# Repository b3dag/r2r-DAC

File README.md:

# r2r-DAC
DIY r2r dac using i2s wich get converted by another board.

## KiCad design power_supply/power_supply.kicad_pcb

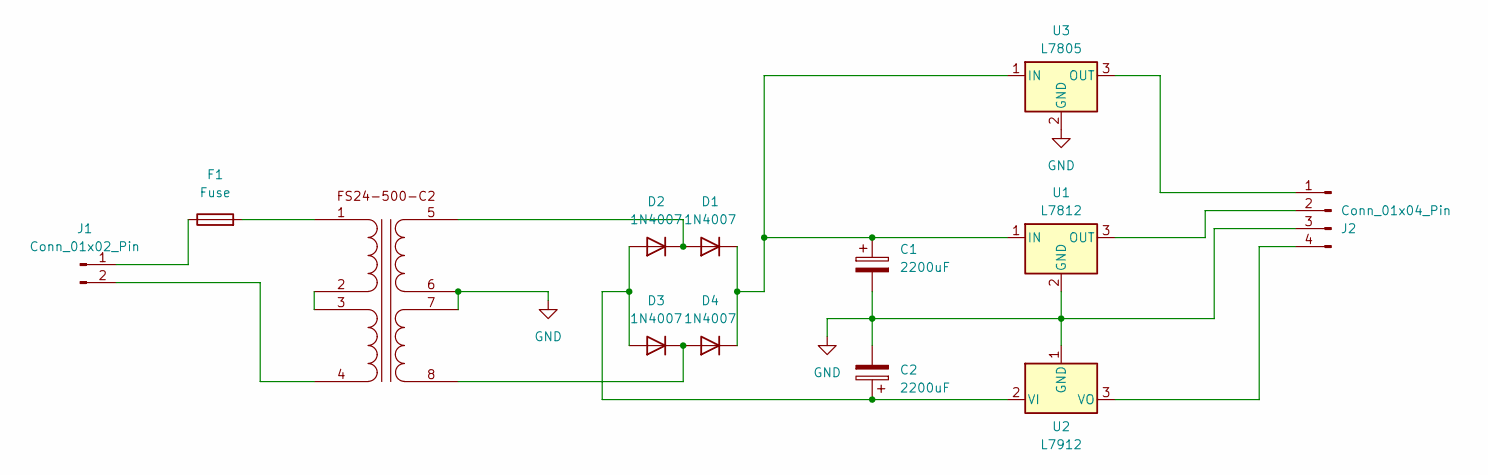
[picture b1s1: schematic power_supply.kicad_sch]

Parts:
C1, C2: 2200uF; CP_Radial_D12.5mm_P5.00mm
D1, D2, D3, D4: 1N4007; D_DO-41_SOD81_P10.16mm_Horizontal
F1: Fuse; Fuseholder_Clip-5x20mm_Littelfuse_111_Inline_P20.00x5.00mm_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
J1: Conn_01x02_Pin; SolderWire-0.5sqmm_1x02_P4.6mm_D0.9mm_OD2.1mm
J2: Conn_01x04_Pin; SolderWire-0.5sqmm_1x04_P4.6mm_D0.9mm_OD2.1mm
T1: FS24-500-C2
U1: L7812; TO-220-3_Vertical
U2: L7912; TO-220-3_Vertical
U3: L7805; TO-220-3_Vertical

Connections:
GND: C1.2, C2.2, J2.3, T1.6, T1.7, U1.2 (GND), U2.1 (GND), U3.2 (GND)
unnamed: D1.2 (A), D2.1 (K), T1.5
unnamed: C1.1, D1.1 (K), D4.1 (K), U1.1 (IN), U3.1 (IN)
unnamed: C2.1, D2.2 (A), D3.2 (A), U2.2 (VI)
unnamed: D3.1 (K), D4.2 (A), T1.8
unnamed: F1.2, T1.1
unnamed 6: F1.1, J1.1; also elsewhere on the board
unnamed 7: J1.2, T1.4; also elsewhere on the board
unnamed: J2.1, U3.3 (OUT)
unnamed: J2.2, U1.3 (OUT)
unnamed: J2.4, U2.3 (VO)
unnamed: T1.2, T1.3

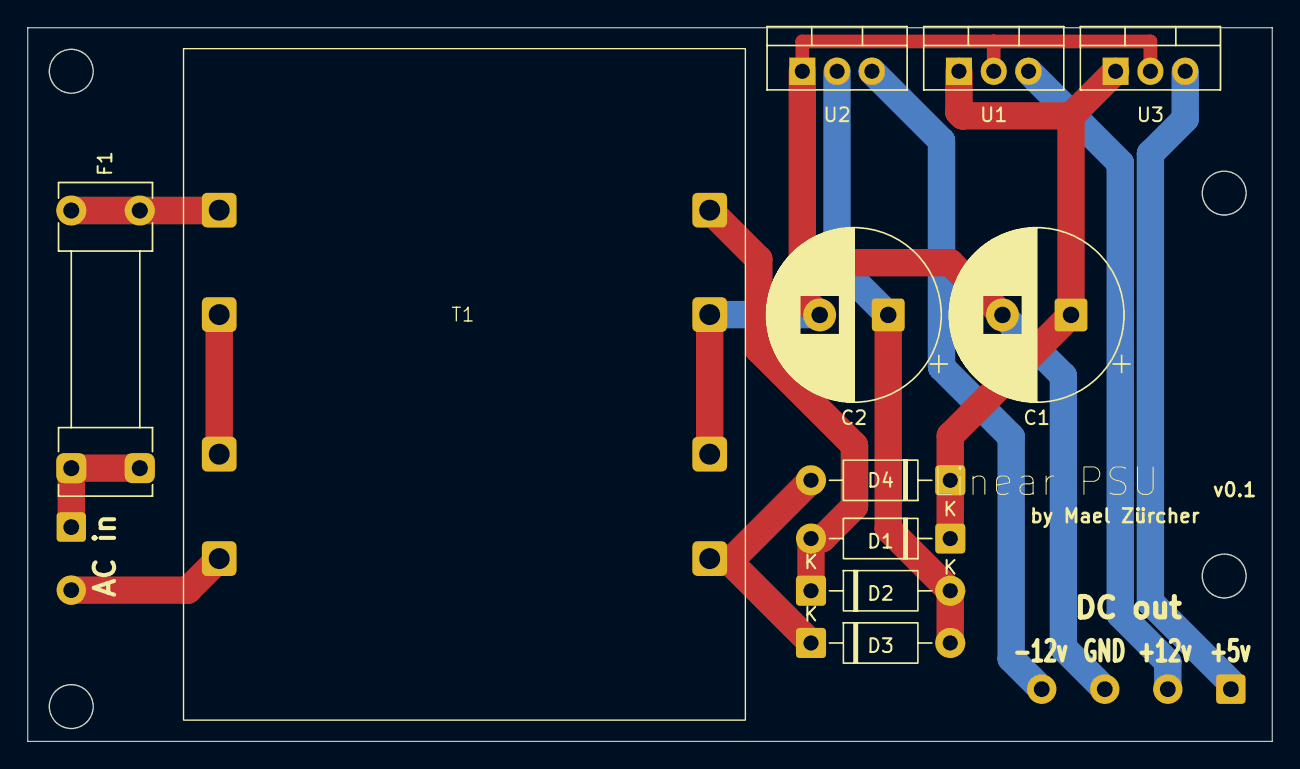
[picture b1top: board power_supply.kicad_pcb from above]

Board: 2 copper layers, 90.8 x 52.1 mm, 13 parts (0 on the bottom side), 12 nets.

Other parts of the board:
AC in: Conn_01x02_Pin; SolderWire-0.5sqmm_1x02_P4.6mm_D0.9mm_OD2.1mm

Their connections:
unnamed 6: AC in.1; also elsewhere on the board
unnamed 7: AC in.2; also elsewhere on the board

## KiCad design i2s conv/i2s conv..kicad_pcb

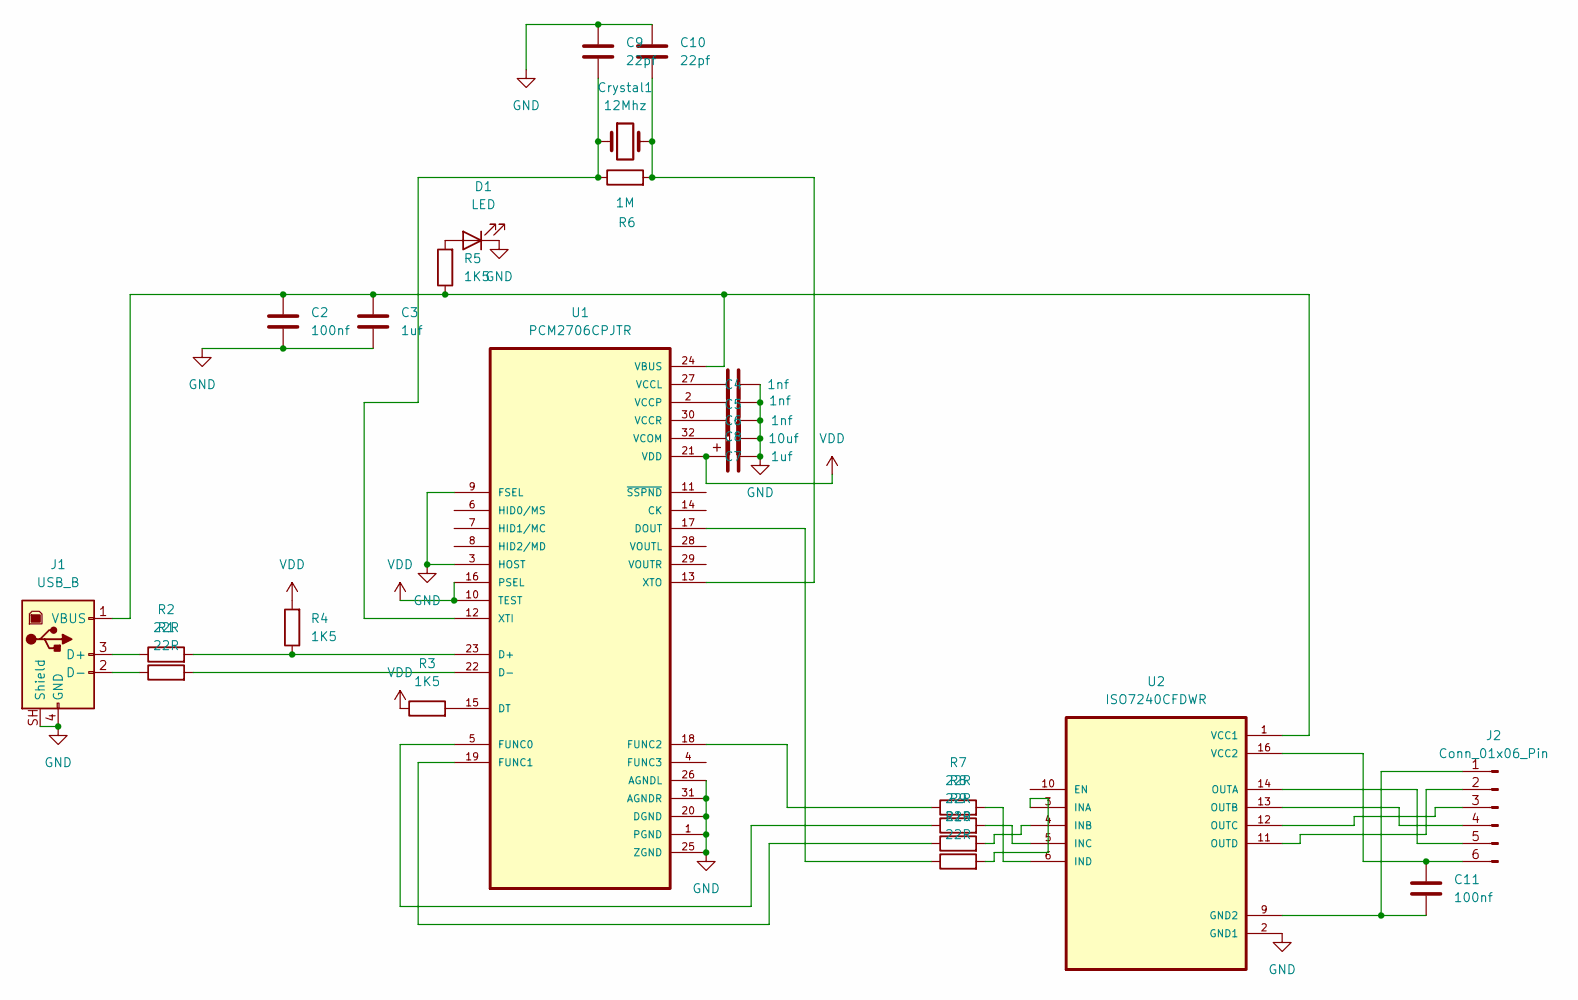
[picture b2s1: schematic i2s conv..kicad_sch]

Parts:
C2, C11: 100nf; C_0805_2012Metric_Pad1.18x1.45mm_HandSolder
C3, C7: 1uf; C_0805_2012Metric_Pad1.18x1.45mm_HandSolder
C4, C5, C6: 1nf; C_0805_2012Metric_Pad1.18x1.45mm_HandSolder
C8: 10uf; C_Radial_D6.3mm_H7.0mm_P2.50mm
C9, C10: 22pf; C_0805_2012Metric_Pad1.18x1.45mm_HandSolder
Crystal1: 12Mhz; Crystal_HC49-4H_Vertical
D1: LED; LED_D5.0mm
J1: USB_B; USB_B_OST_USB-B1HSxx_Horizontal
J2: Conn_01x06_Pin; PinHeader_1x06_P2.54mm_Vertical
R1, R2, R7, R8, R9, R10: 22R; R_0805_2012Metric_Pad1.20x1.40mm_HandSolder
R3, R4, R5: 1K5; R_0805_2012Metric_Pad1.20x1.40mm_HandSolder
R6: 1M; R_0805_2012Metric_Pad1.20x1.40mm_HandSolder
U1: PCM2706CPJTR; QFP80P900X900X120-32N
U2: ISO7240CFDWR; SOIC127P1030X265-16N

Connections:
GND: C2.2, C3.2, C4.2, C5.2, C6.2, C7.2, C8.2, C9.1, C10.1, D1.1 (K), J1.4 (GND), J1.SH (Shield), U1.1 (PGND), U1.3 (HOST), U1.9 (FSEL), U1.20 (DGND), U1.25 (ZGND), U1.26 (AGNDL), U1.31 (AGNDR), U2.2 (GND1), U2.8 (GND1)
GND2: C11.2, J2.1, U2.9 (GND2), U2.15 (GND2)
unnamed: D1.2 (A), R5.2
unnamed: J1.3 (D+), R2.1
unnamed: J1.2 (D-), R1.1
unnamed: C2.1, C3.1, J1.1 (VBUS), R5.1, U1.24 (VBUS), U2.1 (VCC1)
unnamed: J2.2, U2.11 (OUTD)
unnamed: J2.3, U2.12 (OUTC)
unnamed: J2.4, U2.13 (OUTB)
unnamed: J2.5, U2.14 (OUTA)
unnamed: C11.1, J2.6, U2.16 (VCC2)
unnamed: R2.2, R4.1, U1.23 (D+)
unnamed: R1.2, U1.22 (D-)
unnamed: R10.1, U1.17 (DOUT)
unnamed: R3.2, U1.15 (DT)
unnamed: R8.1, U1.5 (FUNC0)
unnamed: R9.1, U1.19 (FUNC1)
unnamed: R7.1, U1.18 (FUNC2)
unnamed: C4.1, U1.27 (VCCL)
unnamed: C5.1, U1.2 (VCCP)
unnamed: C6.1, U1.30 (VCCR)
unnamed: C8.1, U1.32 (VCOM)
unnamed: C9.2, Crystal1.1, R6.1, U1.12 (XTI)
unnamed: C10.2, Crystal1.2, R6.2, U1.13 (XTO)
unnamed: R10.2, U2.3 (INA)
unnamed: R9.2, U2.4 (INB)
unnamed: R8.2, U2.5 (INC)
unnamed: R7.2, U2.6 (IND)
VDD: C7.1, R3.1, R4.2, U1.10 (TEST), U1.16 (PSEL), U1.21 (VDD)

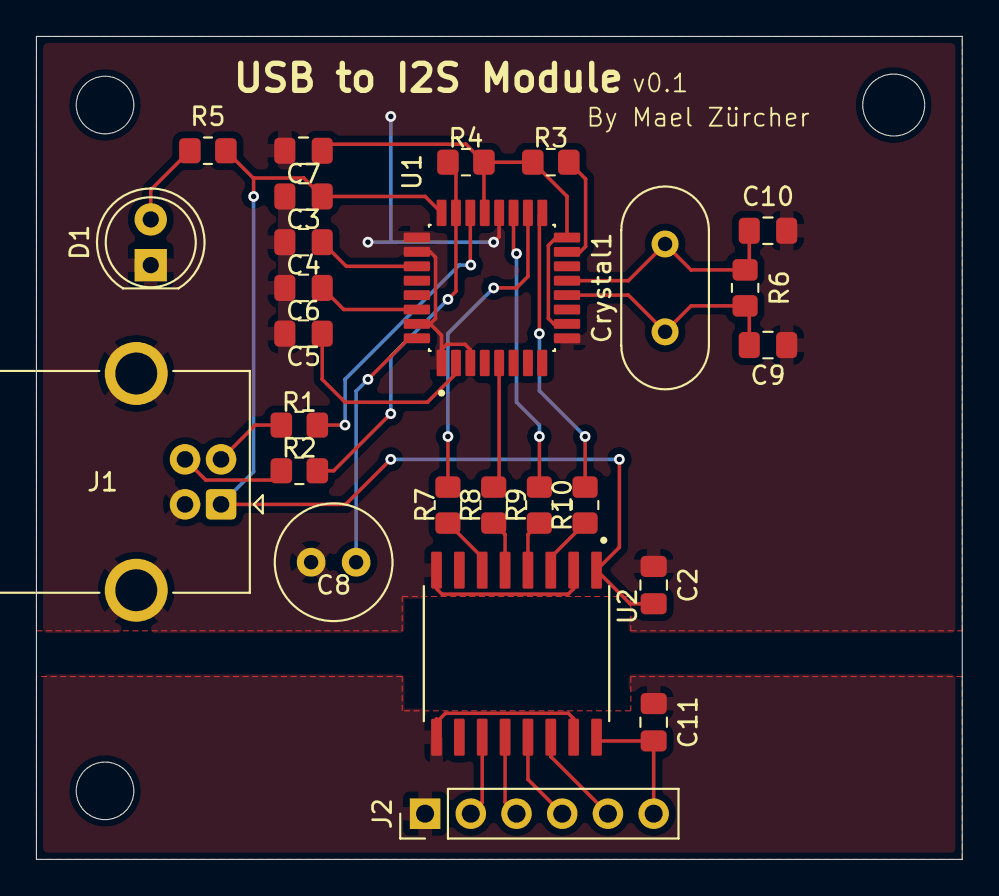
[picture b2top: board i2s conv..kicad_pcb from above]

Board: 2 copper layers, 51.4 x 45.7 mm, 26 parts (0 on the bottom side), 29 nets.

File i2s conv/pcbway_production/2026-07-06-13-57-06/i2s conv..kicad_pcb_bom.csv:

Designator,Quantity,Value,Footprint,Package,MPN,DNP,Mount_Type,Description,KiLib_Generator,Sim.Pins,MF,Price,SnapEDA_Link,MP,Availability,Check_prices
"C10, C9",2,22pf,C_0805_2012Metric_Pad1.18x1.45mm_HandSolder,,,,smt,Unpolarized capacitor,SMD_2terminal_chip_molded,,,,,,,
"C11, C2",2,100nf,C_0805_2012Metric_Pad1.18x1.45mm_HandSolder,,,,smt,Unpolarized capacitor,SMD_2terminal_chip_molded,,,,,,,
"C3, C7",2,1uf,C_0805_2012Metric_Pad1.18x1.45mm_HandSolder,,,,smt,Unpolarized capacitor,SMD_2terminal_chip_molded,,,,,,,
"C4, C5, C6",3,1nf,C_0805_2012Metric_Pad1.18x1.45mm_HandSolder,,,,smt,Unpolarized capacitor,SMD_2terminal_chip_molded,,,,,,,
C8,1,10uf,C_Radial_D6.3mm_H7.0mm_P2.50mm,,,,tht,Polarized capacitor,capacitor/THT/other,,,,,,,
Crystal1,1,12Mhz,Crystal_HC49-4H_Vertical,,,,tht,Two pin crystal,crystal_resonator_oscillator,,,,,,,
D1,1,LED,LED_D5.0mm,,,,tht,Light emitting diode,LED/THT,1=K 2=A,,,,,,
J1,1,USB_B,USB_B_OST_USB-B1HSxx_Horizontal,,,,tht,USB Type B connector,,,,,,,,
J2,1,Conn_01x06_Pin,PinHeader_1x06_P2.54mm_Vertical,,,,tht,"Generic connector, single row, 01x06, script generated",connector/pin_header_socket,,,,,,,
"R1, R10, R2, R7, R8, R9",6,22R,R_0805_2012Metric_Pad1.20x1.40mm_HandSolder,,,,smt,Resistor,SMD_2terminal_chip_molded,,,,,,,
"R3, R4, R5",3,1K5,R_0805_2012Metric_Pad1.20x1.40mm_HandSolder,,,,smt,Resistor,SMD_2terminal_chip_molded,,,,,,,
R6,1,1M,R_0805_2012Metric_Pad1.20x1.40mm_HandSolder,,,,smt,Resistor,SMD_2terminal_chip_molded,,,,,,,
U1,1,PCM2706CPJTR,QFP80P900X900X120-32N,TQFP-32 Texas Instruments,,,smt,"98dB SNR Stereo Full Speed DAC with line-out and S/PDIF output, Bus/Self-powered (I2S)",,,Texas Instruments,None,https://www.snapeda.com/parts/PCM2706CPJTR/Texas+Instruments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,PCM2706CPJTR,In Stock,https://www.snapeda.com/parts/PCM2706CPJTR/Texas+Instruments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
U2,1,ISO7240CFDWR,SOIC127P1030X265-16N,SOIC-16 Texas Instruments,,,smt,"Quad-channel, 4/0, 25-Mbps, default output low digital isolator",,,Texas Instruments,None,https://www.snapeda.com/parts/ISO7240CFDWR/Texas+Instruments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,ISO7240CFDWR,In Stock,https://www.snapeda.com/parts/ISO7240CFDWR/Texas+Instruments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

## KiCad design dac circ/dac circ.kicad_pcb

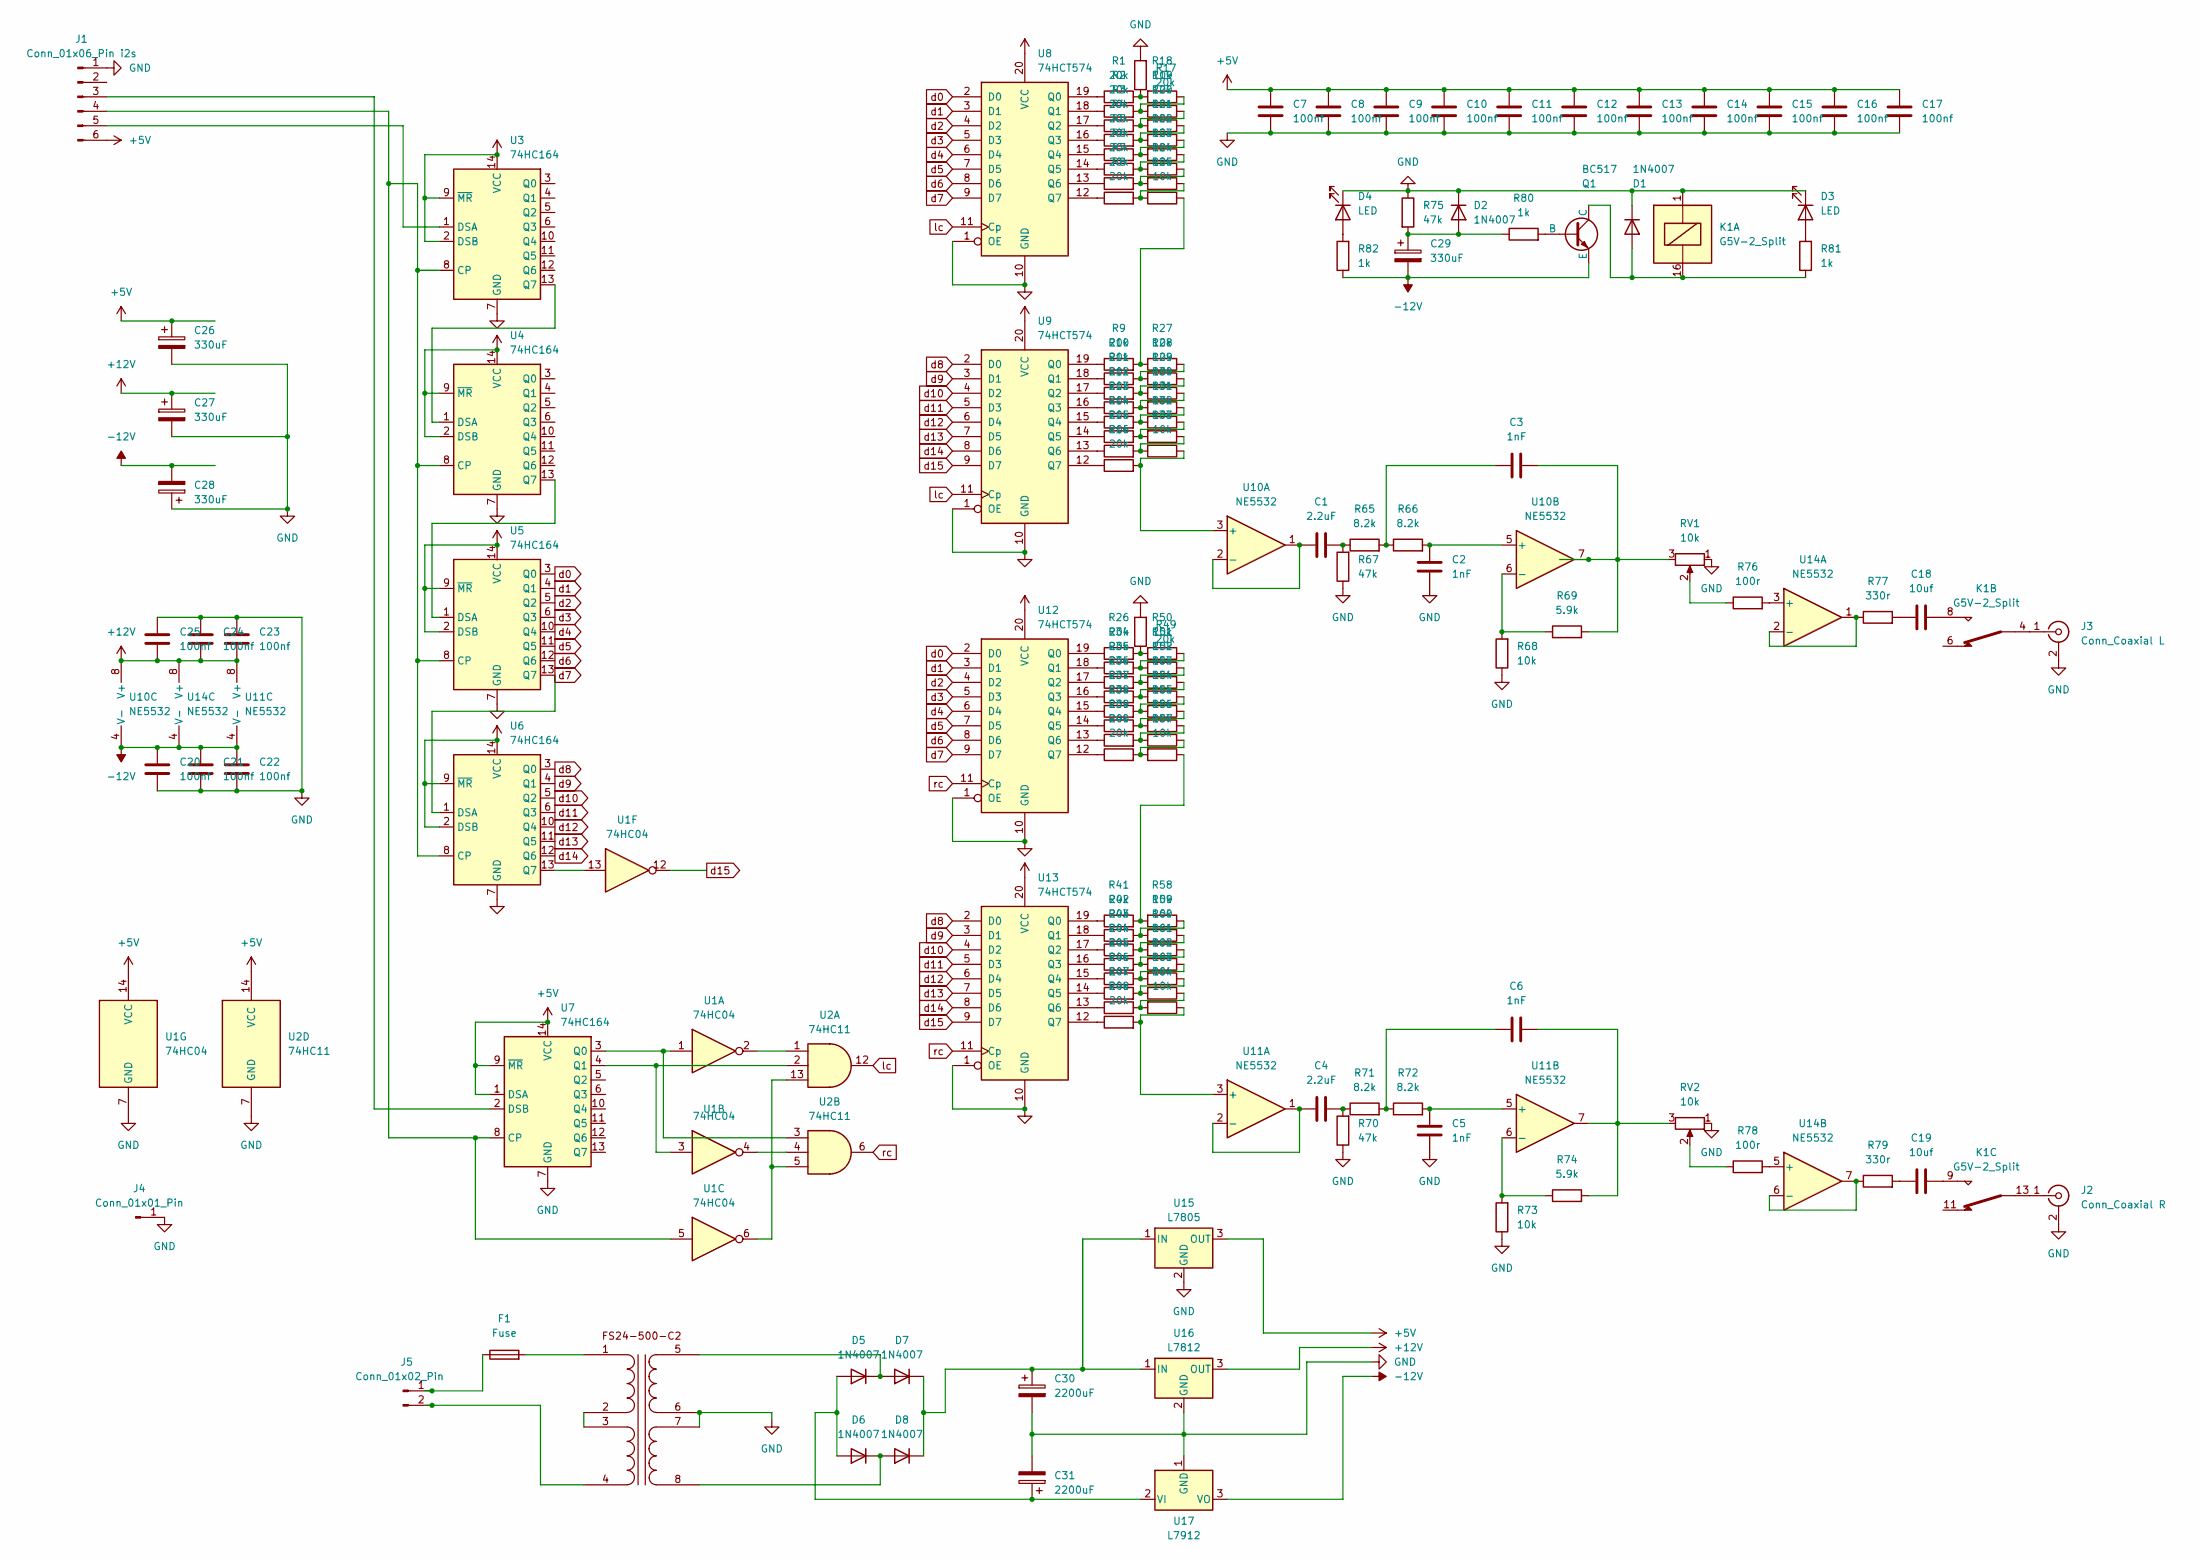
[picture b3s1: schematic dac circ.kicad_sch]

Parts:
C1, C4: 2.2uF; C_Radial_D5.0mm_H11.0mm_P2.00mm
C2, C3, C5, C6: 1nF; C_Disc_D5.0mm_W2.5mm_P5.00mm
C7, C8, C9, C10, C11, C12, C13, C14, C15, C16, C17, C20, C21, C22, C23, C24, C25: 100nf; C_Disc_D5.0mm_W2.5mm_P5.00mm
C18, C19: 10uf; C_Radial_D5.0mm_H11.0mm_P2.00mm
C26, C27, C28, C29: 330uF; CP_Radial_D12.5mm_P5.00mm
C30, C31: 2200uF; CP_Radial_D12.5mm_P5.00mm
D1, D2: 1N4007; D_A-405_P7.62mm_Horizontal
D3, D4: LED; LED_D5.0mm
D5, D6, D7, D8: 1N4007; D_DO-41_SOD81_P10.16mm_Horizontal
F1: Fuse; Fuseholder_Clip-5x20mm_Littelfuse_111_Lateral_P18.80x5.00mm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
J1: Conn_01x06_Pin i2s; PinHeader_1x06_P2.54mm_Vertical
J2: Conn_Coaxial R; SolderWire-0.5sqmm_1x02_P4.6mm_D0.9mm_OD2.1mm
J3: Conn_Coaxial L; SolderWire-0.25sqmm_1x02_P4.5mm_D0.65mm_OD2mm
J4: Conn_01x01_Pin; SolderWire-0.5sqmm_1x01_D0.9mm_OD2.1mm
J5: Conn_01x02_Pin; SolderWire-0.5sqmm_1x02_P4.6mm_D0.9mm_OD2.1mm
K1: G5V-2_Split; Relay_DPDT_Omron_G5V-2
Q1: BC517; TO-92L_HandSolder
R1, R2, R3, R4, R5, R6, R7, R8, R9, R10, R11, R12, R13, R14, R15, R16, R17, R26, R34, R35, R36, R37, R38, R39, R40, R41, R42, R43, R44, R45, R46, R47, R48, R49: 20k; R_Axial_DIN0207_L6.3mm_D2.5mm_P7.62mm_Horizontal
R18, R19, R20, R21, R22, R23, R24, R25, R27, R28, R29, R30, R31, R32, R33, R50, R51, R52, R53, R54, R55, R56, R57, R58, R59, R60, R61, R62, R63, R64, R68, R73: 10k; R_Axial_DIN0207_L6.3mm_D2.5mm_P7.62mm_Horizontal
R65, R66, R71, R72: 8.2k; R_Axial_DIN0207_L6.3mm_D2.5mm_P7.62mm_Horizontal
R67, R70, R75: 47k; R_Axial_DIN0207_L6.3mm_D2.5mm_P7.62mm_Horizontal
R69, R74: 5.9k; R_Axial_DIN0207_L6.3mm_D2.5mm_P7.62mm_Horizontal
R76, R78: 100r; R_Axial_DIN0207_L6.3mm_D2.5mm_P7.62mm_Horizontal
R77, R79: 330r; R_Axial_DIN0207_L6.3mm_D2.5mm_P7.62mm_Horizontal
R80, R81, R82: 1k; R_Axial_DIN0207_L6.3mm_D2.5mm_P7.62mm_Horizontal
RV1, RV2: 10k; Potentiometer_Bourns_3296W_Vertical
T1: TRANSFORMER_FS24-500-C2
U1: 74HC04; DIP-14_W7.62mm
U2: 74HC11; DIP-14_W7.62mm
U3, U4, U5, U6, U7: 74HC164; DIP-14_W7.62mm
U8, U9, U12, U13: 74HCT574; DIP-20_W7.62mm
U10, U11, U14: NE5532; DIP-8_W7.62mm
U15: L7805; TO-220-3_Horizontal_TabUp
U16: L7812; TO-220-3_Horizontal_TabUp
U17: L7912; TO-220-3_Horizontal_TabUp

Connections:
+5V: C7.1, C8.1, C9.1, C10.1, C11.1, C12.1, C13.1, C14.1, C15.1, C16.1, C17.1, C26.1, J1.6, U1.14 (VCC), U2.14 (VCC), U3.2 (DSB), U3.9 (~MR), U3.14 (VCC), U4.2 (DSB), U4.9 (~MR), U4.14 (VCC), U5.2 (DSB), U5.9 (~MR), U5.14 (VCC), U6.2 (DSB), U6.9 (~MR), U6.14 (VCC), U7.1 (DSA), U7.9 (~MR), U7.14 (VCC), U8.20 (VCC), U9.20 (VCC), U12.20 (VCC), U13.20 (VCC), U15.3 (OUT)
+12V: C23.2, C24.2, C25.2, C27.1, U10.8 (V+), U11.8 (V+), U14.8 (V+), U16.3 (OUT)
-12V: C20.1, C21.1, C22.1, C28.2, C29.2, Q1.3 (E), R82.1, U10.4 (V-), U11.4 (V-), U14.4 (V-), U17.3 (VO)
GND: C2.2, C5.2, C7.2, C8.2, C9.2, C10.2, C11.2, C12.2, C13.2, C14.2, C15.2, C16.2, C17.2, C20.2, C21.2, C22.2, C23.1, C24.1, C25.1, C26.2, C27.2, C28.1, C30.2, C31.2, D1.1 (K), D2.1 (K), D3.1 (K), D4.1 (K), J1.1, J2.2 (Ext), J3.2 (Ext), J4.1 (Pin_1_1), K1.1, R17.2, R49.2, R67.1, R68.1, R70.1, R73.1, R75.1, RV1.1, RV2.1, T1.6, T1.7, U1.7 (GND), U2.7 (GND), U3.7 (GND), U4.7 (GND), U5.7 (GND), U6.7 (GND), U7.7 (GND), U8.1 (OE), U8.10 (GND), U9.1 (OE), U9.10 (GND), U12.1 (OE), U12.10 (GND), U13.1 (OE), U13.10 (GND), U15.2 (GND), U16.2 (GND), U17.1 (GND)
unnamed: C1.2, R65.1, R67.2
unnamed: C3.1, R65.2, R66.1
unnamed: C3.2, R69.2, RV1.3, U10.7
unnamed: C4.2, R70.2, R71.1
unnamed: C6.1, R71.2, R72.1
unnamed: C6.2, R74.2, RV2.3, U11.7
unnamed: C18.1, R77.2
unnamed: C18.2, K1.8
unnamed: C19.1, R79.2
unnamed: C19.2, K1.9
unnamed: D1.2 (A), K1.16, Q1.1 (C), R81.1
unnamed: C29.1, D2.2 (A), R75.2, R80.1
unnamed: D3.2 (A), R81.2
unnamed: D4.2 (A), R82.2
unnamed: C31.1, D5.2 (A), D6.2 (A), U17.2 (VI)
unnamed: D5.1 (K), D7.2 (A), T1.5
unnamed: D6.1 (K), D8.2 (A), T1.8
unnamed: C30.1, D7.1 (K), D8.1 (K), U15.1 (IN), U16.1 (IN)
unnamed: F1.2, T1.1
unnamed: J1.3, U7.2 (DSB)
unnamed: J1.4, U1.5, U3.8 (CP), U4.8 (CP), U5.8 (CP), U6.8 (CP), U7.8 (CP)
unnamed: J1.5, U3.1 (DSA)
unnamed: J2.1 (In), K1.13
unnamed: J3.1 (In), K1.4
unnamed: F1.1, J5.1
unnamed: J5.2, T1.4
unnamed: Q1.2 (B), R80.2
unnamed: R1.2, R17.1, R18.2
unnamed: R10.2, R27.1, R28.2
unnamed: R11.2, R28.1, R29.2
unnamed: R12.2, R29.1, R30.2
unnamed: R13.2, R30.1, R31.2
unnamed: R14.2, R31.1, R32.2
unnamed: R15.2, R32.1, R33.2
unnamed: R2.2, R18.1, R19.2
unnamed: R3.2, R19.1, R20.2
unnamed: R4.2, R20.1, R21.2
unnamed: R5.2, R21.1, R22.2
unnamed: R6.2, R22.1, R23.2
unnamed: R7.2, R23.1, R24.2
unnamed: R8.2, R24.1, R25.2
unnamed: R9.2, R25.1, R27.2
unnamed: R26.2, R49.1, R50.2
unnamed: R34.2, R50.1, R51.2
unnamed: R35.2, R51.1, R52.2
unnamed: R36.2, R52.1, R53.2
unnamed: R37.2, R53.1, R54.2
unnamed: R38.2, R54.1, R55.2
unnamed: R39.2, R55.1, R56.2
unnamed: R40.2, R56.1, R57.2
unnamed: R41.2, R57.1, R58.2
unnamed: R42.2, R58.1, R59.2
unnamed: R43.2, R59.1, R60.2
unnamed: R44.2, R60.1, R61.2
unnamed: R45.2, R61.1, R62.2
unnamed: R46.2, R62.1, R63.2
unnamed: R47.2, R63.1, R64.2
unnamed: R76.1, RV1.2
unnamed: R78.1, RV2.2
unnamed: T1.2, T1.3
unnamed: U1.2, U2.1
unnamed: U1.4, U2.4
unnamed: U1.6, U2.5, U2.13
unnamed: U3.13 (Q7), U4.1 (DSA)
unnamed: U4.13 (Q7), U5.1 (DSA)
unnamed: U1.13, U6.13 (Q7)
unnamed: U1.1, U2.3, U7.3 (Q0)
unnamed: U1.3, U2.2, U7.4 (Q1)
unnamed: R1.1, U8.19 (Q0)
unnamed: R2.1, U8.18 (Q1)
unnamed: R3.1, U8.17 (Q2)
unnamed: R4.1, U8.16 (Q3)
unnamed: R5.1, U8.15 (Q4)
unnamed: R6.1, U8.14 (Q5)
unnamed: R7.1, U8.13 (Q6)
unnamed: R8.1, U8.12 (Q7)
unnamed: R9.1, U9.19 (Q0)
unnamed: R10.1, U9.18 (Q1)
unnamed: R11.1, U9.17 (Q2)
unnamed: R12.1, U9.16 (Q3)
unnamed: R13.1, U9.15 (Q4)
unnamed: R14.1, U9.14 (Q5)
unnamed: R15.1, U9.13 (Q6)
unnamed: R16.1, U9.12 (Q7)
unnamed: R16.2, R33.1, U10.3 (+)
unnamed: C1.1, U10.1, U10.2 (-)
unnamed: C2.1, R66.2, U10.5 (+)
unnamed: R68.2, R69.1, U10.6 (-)
unnamed: R48.2, R64.1, U11.3 (+)
unnamed: C4.1, U11.1, U11.2 (-)
unnamed: C5.1, R72.2, U11.5 (+)
unnamed: R73.2, R74.1, U11.6 (-)
unnamed: R26.1, U12.19 (Q0)
unnamed: R34.1, U12.18 (Q1)
unnamed: R35.1, U12.17 (Q2)
unnamed: R36.1, U12.16 (Q3)
unnamed: R37.1, U12.15 (Q4)
unnamed: R38.1, U12.14 (Q5)
unnamed: R39.1, U12.13 (Q6)
unnamed: R40.1, U12.12 (Q7)
unnamed: R41.1, U13.19 (Q0)
unnamed: R42.1, U13.18 (Q1)
unnamed: R43.1, U13.17 (Q2)
unnamed: R44.1, U13.16 (Q3)
unnamed: R45.1, U13.15 (Q4)
unnamed: R46.1, U13.14 (Q5)
unnamed: R47.1, U13.13 (Q6)
unnamed: R48.1, U13.12 (Q7)
unnamed: R76.2, U14.3 (+)
unnamed: R77.1, U14.1, U14.2 (-)
unnamed: R78.2, U14.5 (+)
unnamed: R79.1, U14.6 (-), U14.7
d0: U5.3 (Q0), U8.2 (D0), U12.2 (D0)
d1: U5.4 (Q1), U8.3 (D1), U12.3 (D1)
d2: U5.5 (Q2), U8.4 (D2), U12.4 (D2)
d3: U5.6 (Q3), U8.5 (D3), U12.5 (D3)
d4: U5.10 (Q4), U8.6 (D4), U12.6 (D4)
d5: U5.11 (Q5), U8.7 (D5), U12.7 (D5)
d6: U5.12 (Q6), U8.8 (D6), U12.8 (D6)
d7: U5.13 (Q7), U6.1 (DSA), U8.9 (D7), U12.9 (D7)
d8: U6.3 (Q0), U9.2 (D0), U13.2 (D0)
d9: U6.4 (Q1), U9.3 (D1), U13.3 (D1)
d10: U6.5 (Q2), U9.4 (D2), U13.4 (D2)
d11: U6.6 (Q3), U9.5 (D3), U13.5 (D3)
d12: U6.10 (Q4), U9.6 (D4), U13.6 (D4)
d13: U6.11 (Q5), U9.7 (D5), U13.7 (D5)
d14: U6.12 (Q6), U9.8 (D6), U13.8 (D6)
d15: U1.12, U9.9 (D7), U13.9 (D7)
lc: U2.12, U8.11 (Cp), U9.11 (Cp)
rc: U2.6, U12.11 (Cp), U13.11 (Cp)

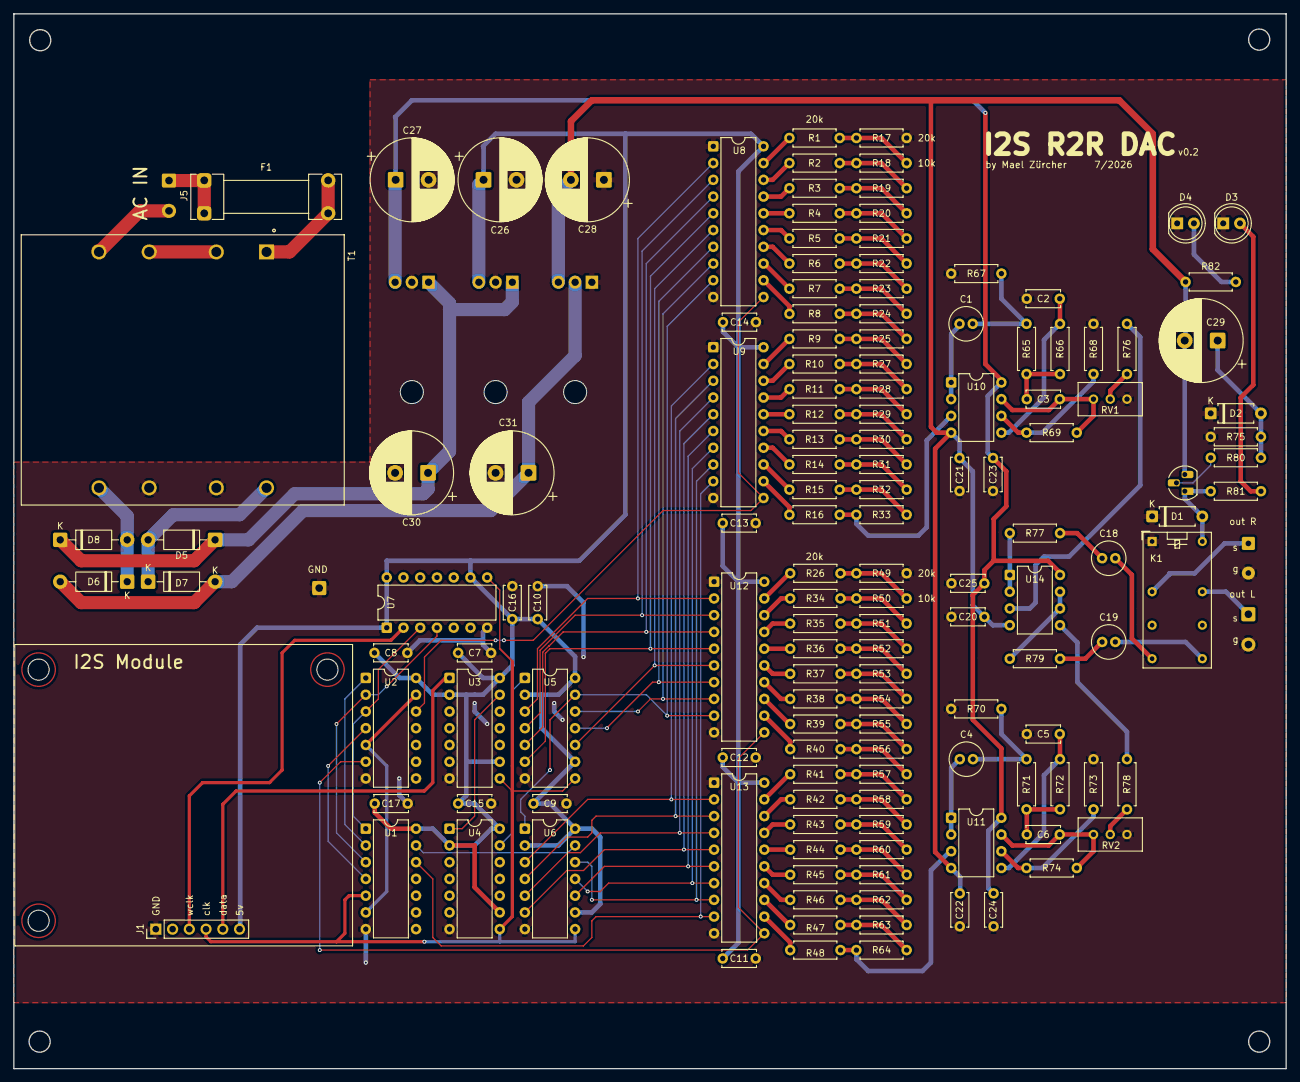
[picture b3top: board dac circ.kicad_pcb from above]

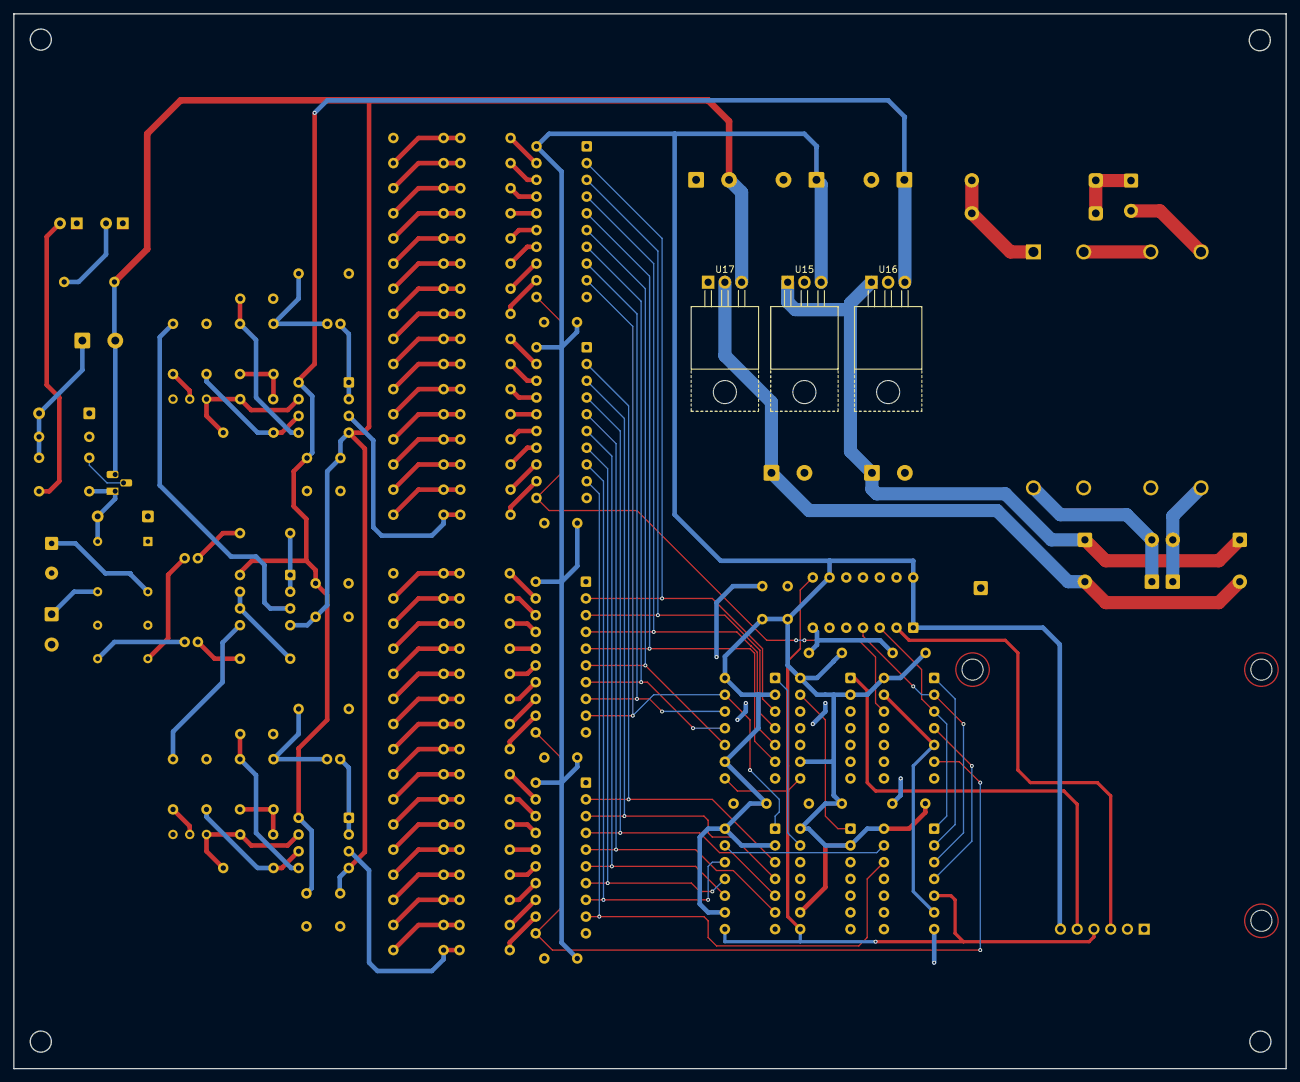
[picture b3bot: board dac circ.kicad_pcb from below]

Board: 2 copper layers, 193.0 x 160.0 mm, 149 parts (3 on the bottom side), 134 nets.

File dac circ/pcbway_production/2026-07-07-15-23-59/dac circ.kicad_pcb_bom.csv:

Designator,Quantity,Value,Footprint,Package,MPN,DNP,Mount_Type,Description,KiLib_Generator,Sim.Device,Sim.Pins,Sim.Type
"C1, C4",2,2.2uF,C_Radial_D5.0mm_H11.0mm_P2.00mm,,,,tht,Unpolarized capacitor,capacitor/THT/other,,,
"C10, C11, C12, C13, C14, C15, C16, C17, C20, C21, C22, C23, C24, C25, C7, C8, C9",17,100nf,C_Disc_D5.0mm_W2.5mm_P5.00mm,,,,tht,Unpolarized capacitor,capacitor/THT/other,,,
"C18, C19",2,10uf,C_Radial_D5.0mm_H11.0mm_P2.00mm,,,,tht,Unpolarized capacitor,capacitor/THT/other,,,
"C2, C3, C5, C6",4,1nF,C_Disc_D5.0mm_W2.5mm_P5.00mm,,,,tht,Unpolarized capacitor,capacitor/THT/other,,,
"C26, C27, C28, C29",4,330uF,CP_Radial_D12.5mm_P5.00mm,,,,tht,Polarized capacitor,capacitor/THT/other,,,
"D1, D2",2,1N4007,D_A-405_P7.62mm_Horizontal,,,,tht,Diode,diode/THT,D,1=K 2=A,
D3,1,LED,LED_D5.0mm,,,,tht,Light emitting diode,LED/THT,,1=K 2=A,
J1,1,Conn_01x06_Pin i2s,PinHeader_1x06_P2.54mm_Vertical,,,,tht,"Generic connector, single row, 01x06, script generated",connector/pin_header_socket,,,
J2,1,Conn_Coaxial R,SolderWire-0.5sqmm_1x02_P4.6mm_D0.9mm_OD2.1mm,,,,tht,"coaxial connector (BNC, SMA, SMB, SMC, Cinch/RCA, LEMO, ...)",connector/wire,,,
J3,1,Conn_Coaxial L,SolderWire-0.25sqmm_1x02_P4.5mm_D0.65mm_OD2mm,,,,tht,"coaxial connector (BNC, SMA, SMB, SMC, Cinch/RCA, LEMO, ...)",connector/wire,,,
J4,1,Conn_01x04_Pin,SolderWire-0.5sqmm_1x04_P4.6mm_D0.9mm_OD2.1mm,,,,tht,"Generic connector, single row, 01x04, script generated",connector/wire,,,
K1,1,G5V-2_Split,Relay_DPDT_Omron_G5V-2,,,,tht,Relay Miniature Omron DPDT,,,,
Q1,1,BC517,TO-92L_HandSolder,,,,tht,"Bipolar transistor symbol for simulation only, substrate tied to the emitter",,NPN,1=C 2=B 3=E,GUMMELPOON
"R1, R10, R11, R12, R13, R14, R15, R16, R17, R2, R26, R3, R34, R35, R36, R37, R38, R39, R4, R40, R41, R42, R43, R44, R45, R46, R47, R48, R49, R5, R6, R7, R8, R9",34,20k,R_Axial_DIN0207_L6.3mm_D2.5mm_P7.62mm_Horizontal,,,,tht,Resistor,resistor/THT,,,
"R18, R19, R20, R21, R22, R23, R24, R25, R27, R28, R29, R30, R31, R32, R33, R50, R51, R52, R53, R54, R55, R56, R57, R58, R59, R60, R61, R62, R63, R64, R68, R73",32,10k,R_Axial_DIN0207_L6.3mm_D2.5mm_P7.62mm_Horizontal,,,,tht,Resistor,resistor/THT,,,
"R65, R66, R71, R72",4,8.2k,R_Axial_DIN0207_L6.3mm_D2.5mm_P7.62mm_Horizontal,,,,tht,Resistor,resistor/THT,,,
"R67, R70, R75",3,47k,R_Axial_DIN0207_L6.3mm_D2.5mm_P7.62mm_Horizontal,,,,tht,Resistor,resistor/THT,,,
"R69, R74",2,5.9k,R_Axial_DIN0207_L6.3mm_D2.5mm_P7.62mm_Horizontal,,,,tht,Resistor,resistor/THT,,,
"R76, R78",2,100r,R_Axial_DIN0207_L6.3mm_D2.5mm_P7.62mm_Horizontal,,,,tht,Resistor,resistor/THT,,,
"R77, R79",2,330r,R_Axial_DIN0207_L6.3mm_D2.5mm_P7.62mm_Horizontal,,,,tht,Resistor,resistor/THT,,,
"R80, R81",2,1k,R_Axial_DIN0207_L6.3mm_D2.5mm_P7.62mm_Horizontal,,,,tht,Resistor,resistor/THT,,,
"RV1, RV2",2,10k,Potentiometer_Bourns_3296W_Vertical,,,,tht,Potentiometer,potentiometer/THT,R,1=r0 2=wiper 3=r1,POT
U1,1,74HC04,DIP-14_W7.62mm,,,,tht,Hex Inverter,package/DIP/legacy,,,
"U10, U11, U14",3,NE5532,DIP-8_W7.62mm,,,,tht,"Dual Low-Noise Operational Amplifiers, DIP-8/SOIC-8",package/DIP/legacy,,,
"U12, U13, U8, U9",4,74HCT574,DIP-20_W7.62mm,,,,tht,"8-bit Register, 3-state outputs",package/DIP/legacy,,,
U2,1,74HC11,DIP-14_W7.62mm,,,,tht,Triple 3-input AND,package/DIP/legacy,,,
"U3, U4, U5, U6, U7",5,74HC164,DIP-14_W7.62mm,,,,tht,8-bit serial-in parallel-out shift register,package/DIP/legacy,,,
